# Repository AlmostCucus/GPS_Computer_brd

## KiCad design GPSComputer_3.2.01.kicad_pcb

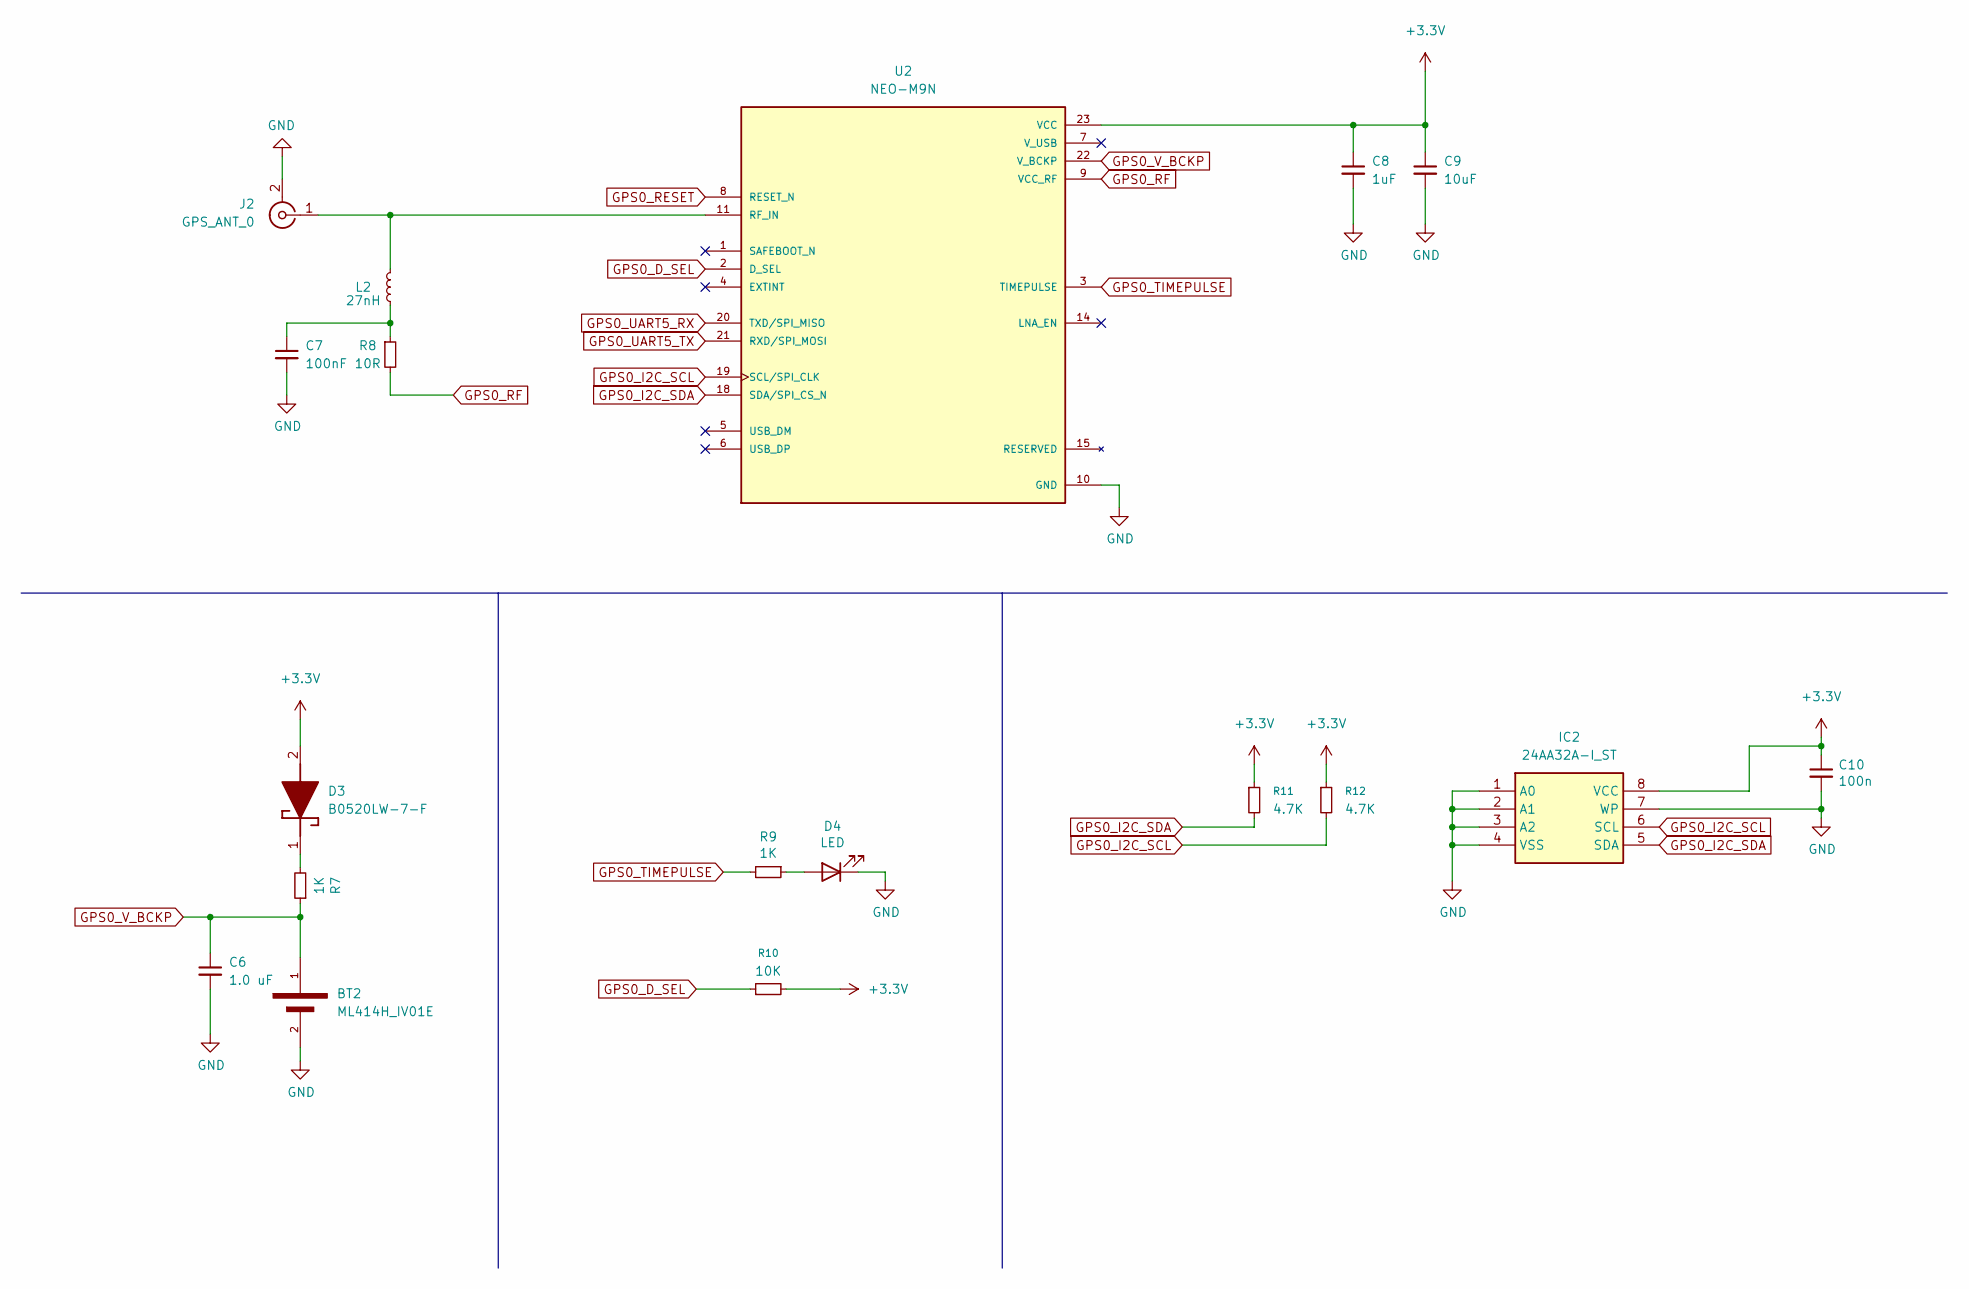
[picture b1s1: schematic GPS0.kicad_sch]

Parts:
BT2: ML414H_IV01E; SEIKO_ML414H_IV01E
C6: 1.0 uF; C_0805_2012Metric
C7: 100nF; C_0402_1005Metric
C8: 1uF; C_1210_3225Metric
C9: 10uF; C_1210_3225Metric
C10: 100n; C_0402_1005Metric
D3: B0520LW-7-F; SOD3716X145N; Manufacturer_Part_Number B0520LW-7-F; Mouser Part Number 621-B0520LW-F
D4: LED; LED_0805_2012Metric_Pad1.15x1.40mm_HandSolder
IC2: 24AA32A-I_ST; SOP65P640X120-8N; Manufacturer_Part_Number 24AA32A-I/ST; Mouser Part Number 579-24AA32A-I/ST
J2: GPS_ANT_0; SMA_Samtec_SMA-J-P-H-ST-EM1_EdgeMount
L2: 27nH; L_0402_1005Metric
R7, R9: 1K; R_0805_2012Metric
R8: 10R; R_0402_1005Metric
R10: 10K; R_0402_1005Metric
R11, R12: 4.7K; R_0402_1005Metric
U2: NEO-M9N; XCVR_NEO-M9N; PARTREV R05

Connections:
+3.3V: C8.1, C9.1, C10.1, D3.2 (A), IC2.8 (VCC), R10.2, R11.1, R12.1, U2.23 (VCC); also elsewhere on the board
GND: BT2.2, C6.2, C7.2, C8.2, C9.2, C10.2, D4.1 (K), IC2.1 (A0), IC2.2 (A1), IC2.3 (A2), IC2.4 (VSS), IC2.7 (WP), J2.2 (Ext), U2.10 (GND), U2.12 (GND), U2.13 (GND), U2.24 (GND); also elsewhere on the board
GPS0_D_SEL: R10.1, U2.2 (D_SEL)
GPS0_I2C_SCL: IC2.6 (SCL), R12.2, U2.19 (SCL/SPI_CLK)
GPS0_I2C_SDA: IC2.5 (SDA), R11.2, U2.18 (SDA/SPI_CS_N)
GPS0_RESET: U2.8 (RESET_N); also elsewhere on the board
GPS0_RF: R8.2, U2.9 (VCC_RF)
GPS0_TIMEPULSE: R9.2, U2.3 (TIMEPULSE)
GPS0_UART5_RX: U2.20 (TXD/SPI_MISO); also elsewhere on the board
GPS0_UART5_TX: U2.21 (RXD/SPI_MOSI); also elsewhere on the board
GPS0_V_BCKP: BT2.1, C6.1, R7.1, U2.22 (V_BCKP)
unnamed: C7.1, L2.1, R8.1
unnamed: D3.1 (K), R7.2
unnamed: D4.2 (A), R9.1
unnamed: J2.1 (In), L2.2, U2.11 (RF_IN)

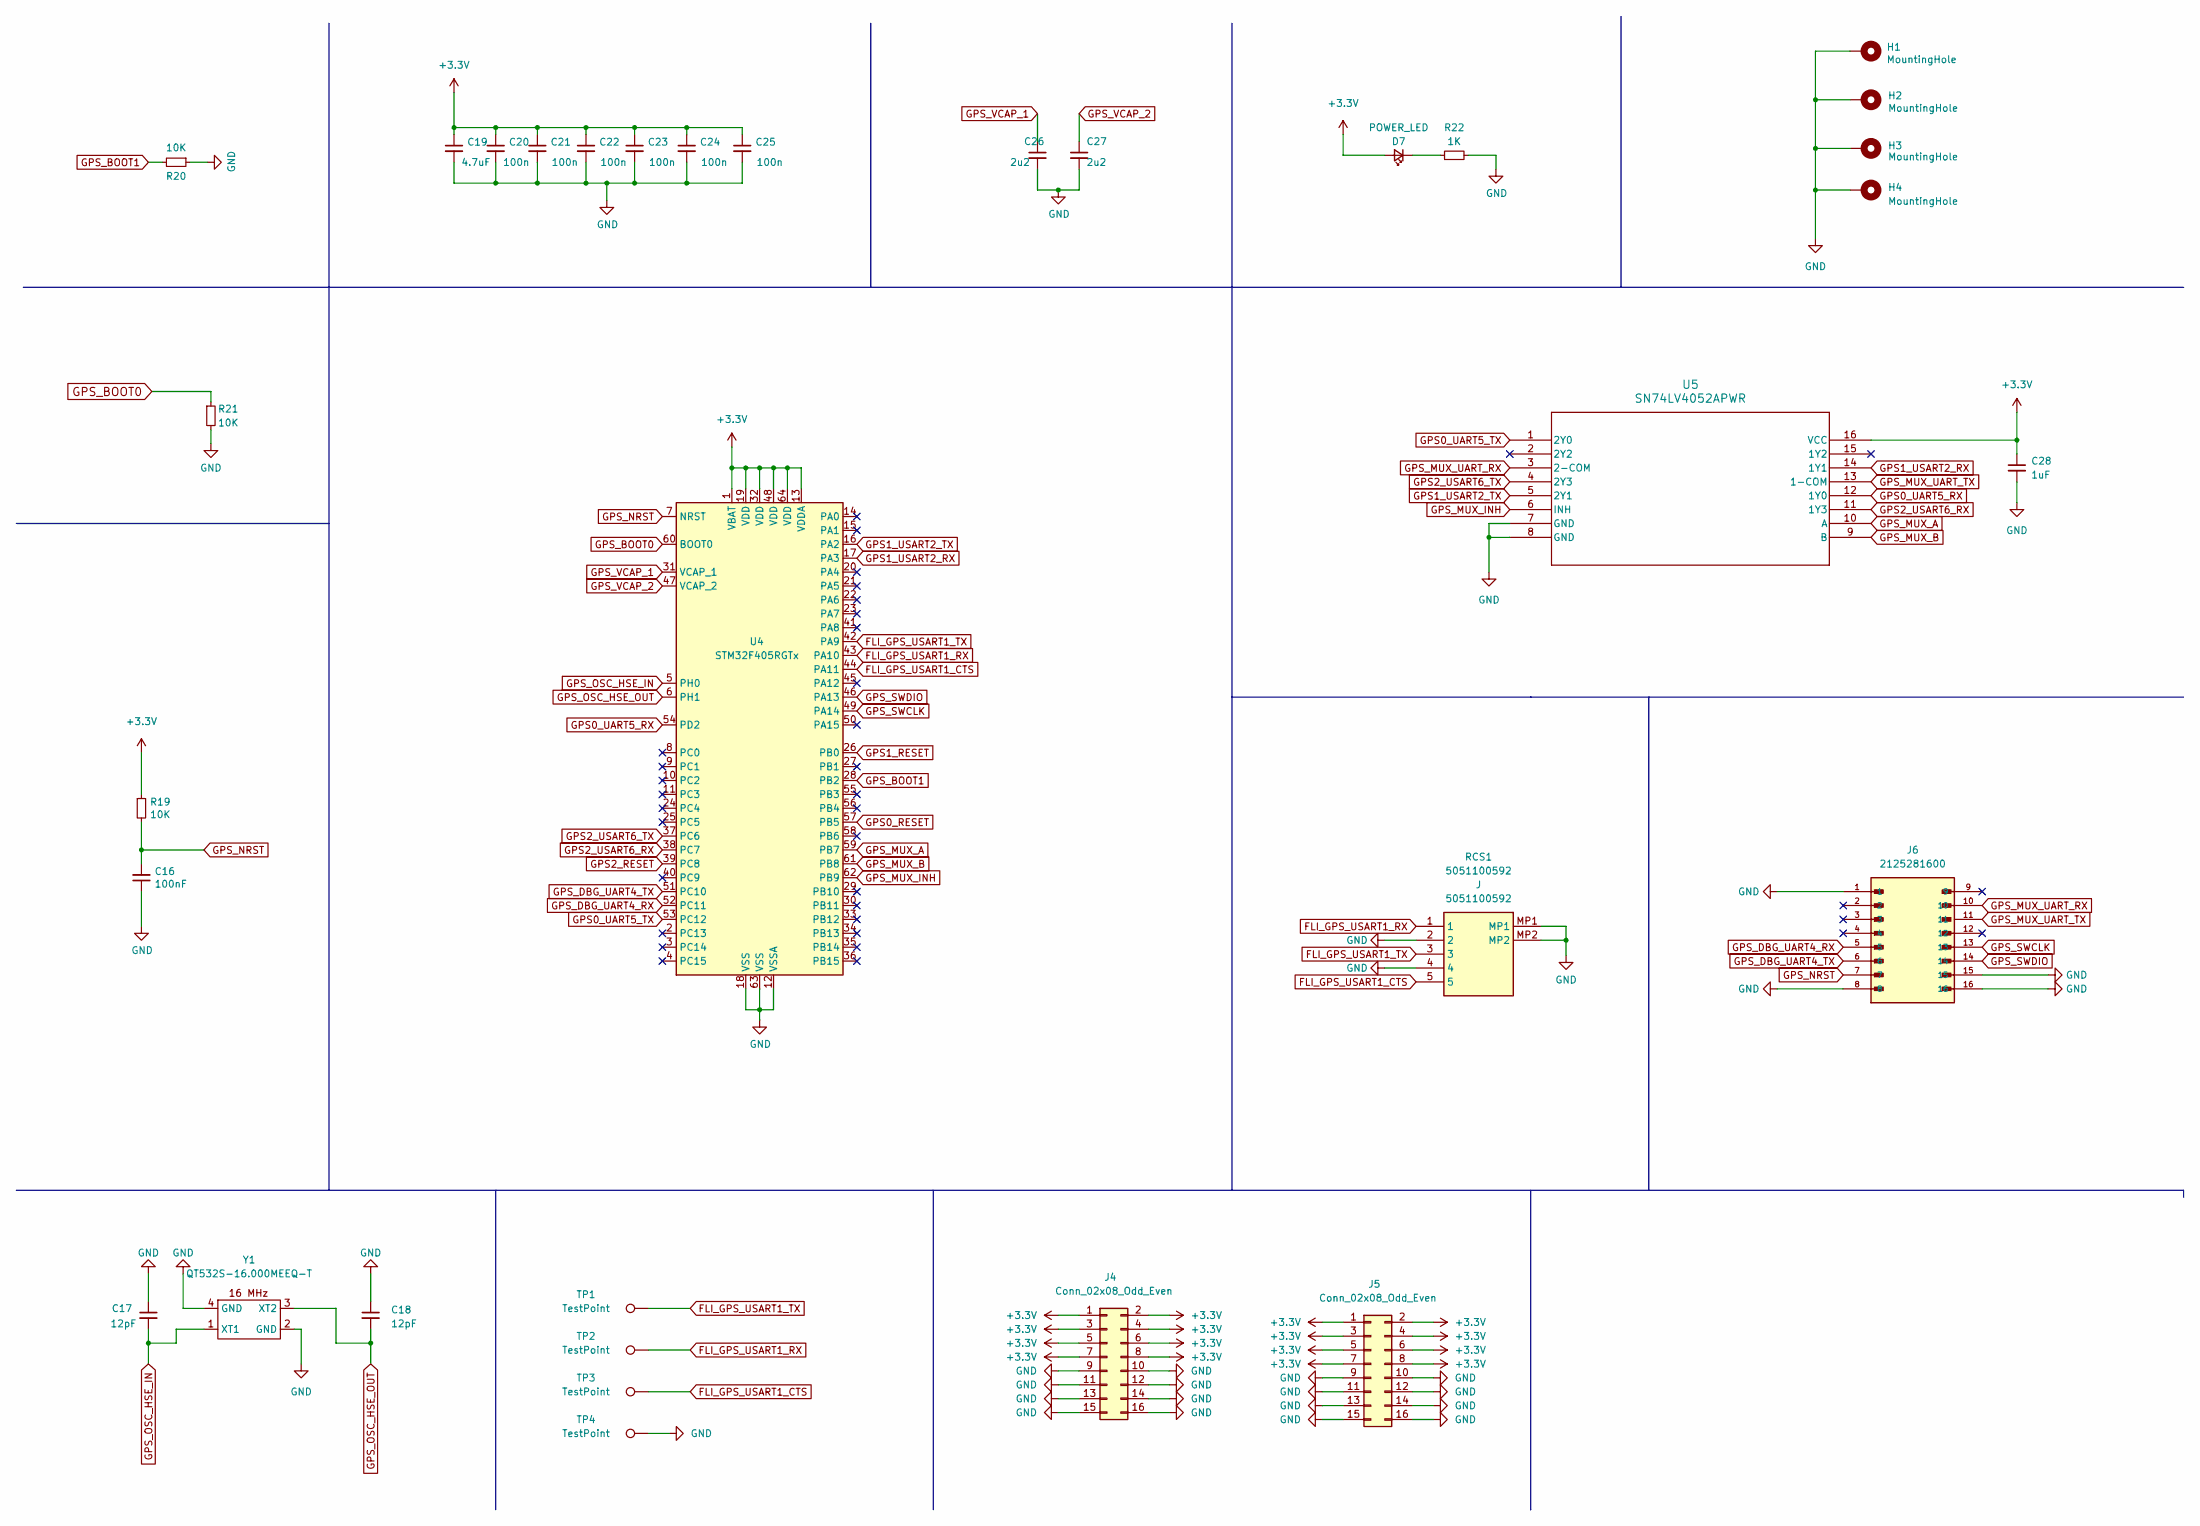
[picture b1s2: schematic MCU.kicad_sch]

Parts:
C16: 100nF; C_0402_1005Metric
C17, C18: 12pF; C_0402_1005Metric
C19: 4.7uF; C_0402_1005Metric
C20, C21, C22, C23, C24, C25: 100n; C_0402_1005Metric
C26, C27: 2u2; C_0603_1608Metric
C28: 1uF; C_0402_1005Metric
D7: POWER_LED; LED_0603_1608Metric
H1, H2, H3, H4: MountingHole; MountingHole_3.2mm_M3_Pad_Via
J4: Conn_02x08_Odd_Even; PinHeader_2x08_P2.54mm_Vertical_SMD
J5: Conn_02x08_Odd_Even; PinSocket_2x08_P2.54mm_Vertical_SMD
J6: 2125281600; MOLEX_2125281600; PARTREV A3
R19, R20, R21: 10K; R_0402_1005Metric
R22: 1K; R_0402_1005Metric
RCS1: 5051100592; Manufacturer_Part_Number 5051100592; Mouser Part Number N/A
TP1, TP2, TP3, TP4: TestPoint; TestPoint_Pad_D1.0mm
U4: STM32F405RGTx; LQFP-64_10x10mm_P0.5mm
U5: SN74LV4052APWR; PW16
Y1: QT532S-16.000MEEQ-T

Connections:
+3.3V: C19.1, C20.1, C21.1, C22.1, C23.1, C24.1, C25.1, C28.1, D7.2 (A), J4.1, J4.2, J4.3, J4.4, J4.5, J4.6, J4.7, J4.8, J5.1, J5.2, J5.3, J5.4, J5.5, J5.6, J5.7, J5.8, R19.1, U4.1 (VBAT), U4.13 (VDDA), U4.19 (VDD), U4.32 (VDD), U4.48 (VDD), U4.64 (VDD), U5.16 (VCC); also elsewhere on the board
FLI_GPS_USART1_CTS: RCS1.5, TP3.1 (1_1), U4.44 (PA11)
FLI_GPS_USART1_RX: RCS1.1, TP2.1 (1_1), U4.43 (PA10)
FLI_GPS_USART1_TX: RCS1.3, TP1.1 (1_1), U4.42 (PA9)
GND: C16.1, C17.1, C18.1, C19.2, C20.2, C21.2, C22.2, C23.2, C24.2, C25.2, C26.2, C27.2, C28.2, H1.1 (1_1), H2.1 (1_1), H3.1 (1_1), H4.1 (1_1), J4.9, J4.10, J4.11, J4.12, J4.13, J4.14, J4.15, J4.16, J5.9, J5.10, J5.11, J5.12, J5.13, J5.14, J5.15, J5.16, J6.1, J6.8, J6.15, J6.16, R20.1, R21.2, R22.2, RCS1.2, RCS1.4, RCS1.MP1, RCS1.MP2, TP4.1 (1_1), U4.12 (VSSA), U4.18 (VSS), U4.63 (VSS), U5.7 (GND), U5.8 (GND), Y1.2 (GND), Y1.4 (GND); also elsewhere on the board
GPS0_RESET: U4.57 (PB5); also elsewhere on the board
GPS0_UART5_RX: U4.54 (PD2), U5.12 (1Y0); also elsewhere on the board
GPS0_UART5_TX: U4.53 (PC12), U5.1 (2Y0); also elsewhere on the board
GPS1_RESET: U4.26 (PB0); also elsewhere on the board
GPS1_USART2_RX: U4.17 (PA3), U5.14 (1Y1); also elsewhere on the board
GPS1_USART2_TX: U4.16 (PA2), U5.5 (2Y1); also elsewhere on the board
GPS2_RESET: U4.39 (PC8); also elsewhere on the board
GPS2_USART6_RX: U4.38 (PC7), U5.11 (1Y3); also elsewhere on the board
GPS2_USART6_TX: U4.37 (PC6), U5.4 (2Y3); also elsewhere on the board
GPS_BOOT0: R21.1, U4.60 (BOOT0)
GPS_BOOT1: R20.2, U4.28 (PB2)
GPS_DBG_UART4_RX: J6.5, U4.52 (PC11)
GPS_DBG_UART4_TX: J6.6, U4.51 (PC10)
GPS_MUX_A: U4.59 (PB7), U5.10 (A)
GPS_MUX_B: U4.61 (PB8), U5.9 (B)
GPS_MUX_INH: U4.62 (PB9), U5.6 (INH)
GPS_MUX_UART_RX: J6.10, U5.3 (2-COM)
GPS_MUX_UART_TX: J6.11, U5.13 (1-COM)
GPS_NRST: C16.2, J6.7, R19.2, U4.7 (NRST)
GPS_OSC_HSE_IN: C17.2, U4.5 (PH0), Y1.1 (XT1)
GPS_OSC_HSE_OUT: C18.2, U4.6 (PH1), Y1.3 (XT2)
GPS_SWCLK: J6.13, U4.49 (PA14)
GPS_SWDIO: J6.14, U4.46 (PA13)
GPS_VCAP_1: C26.1, U4.31 (VCAP_1)
GPS_VCAP_2: C27.1, U4.47 (VCAP_2)
unnamed: D7.1 (K), R22.1

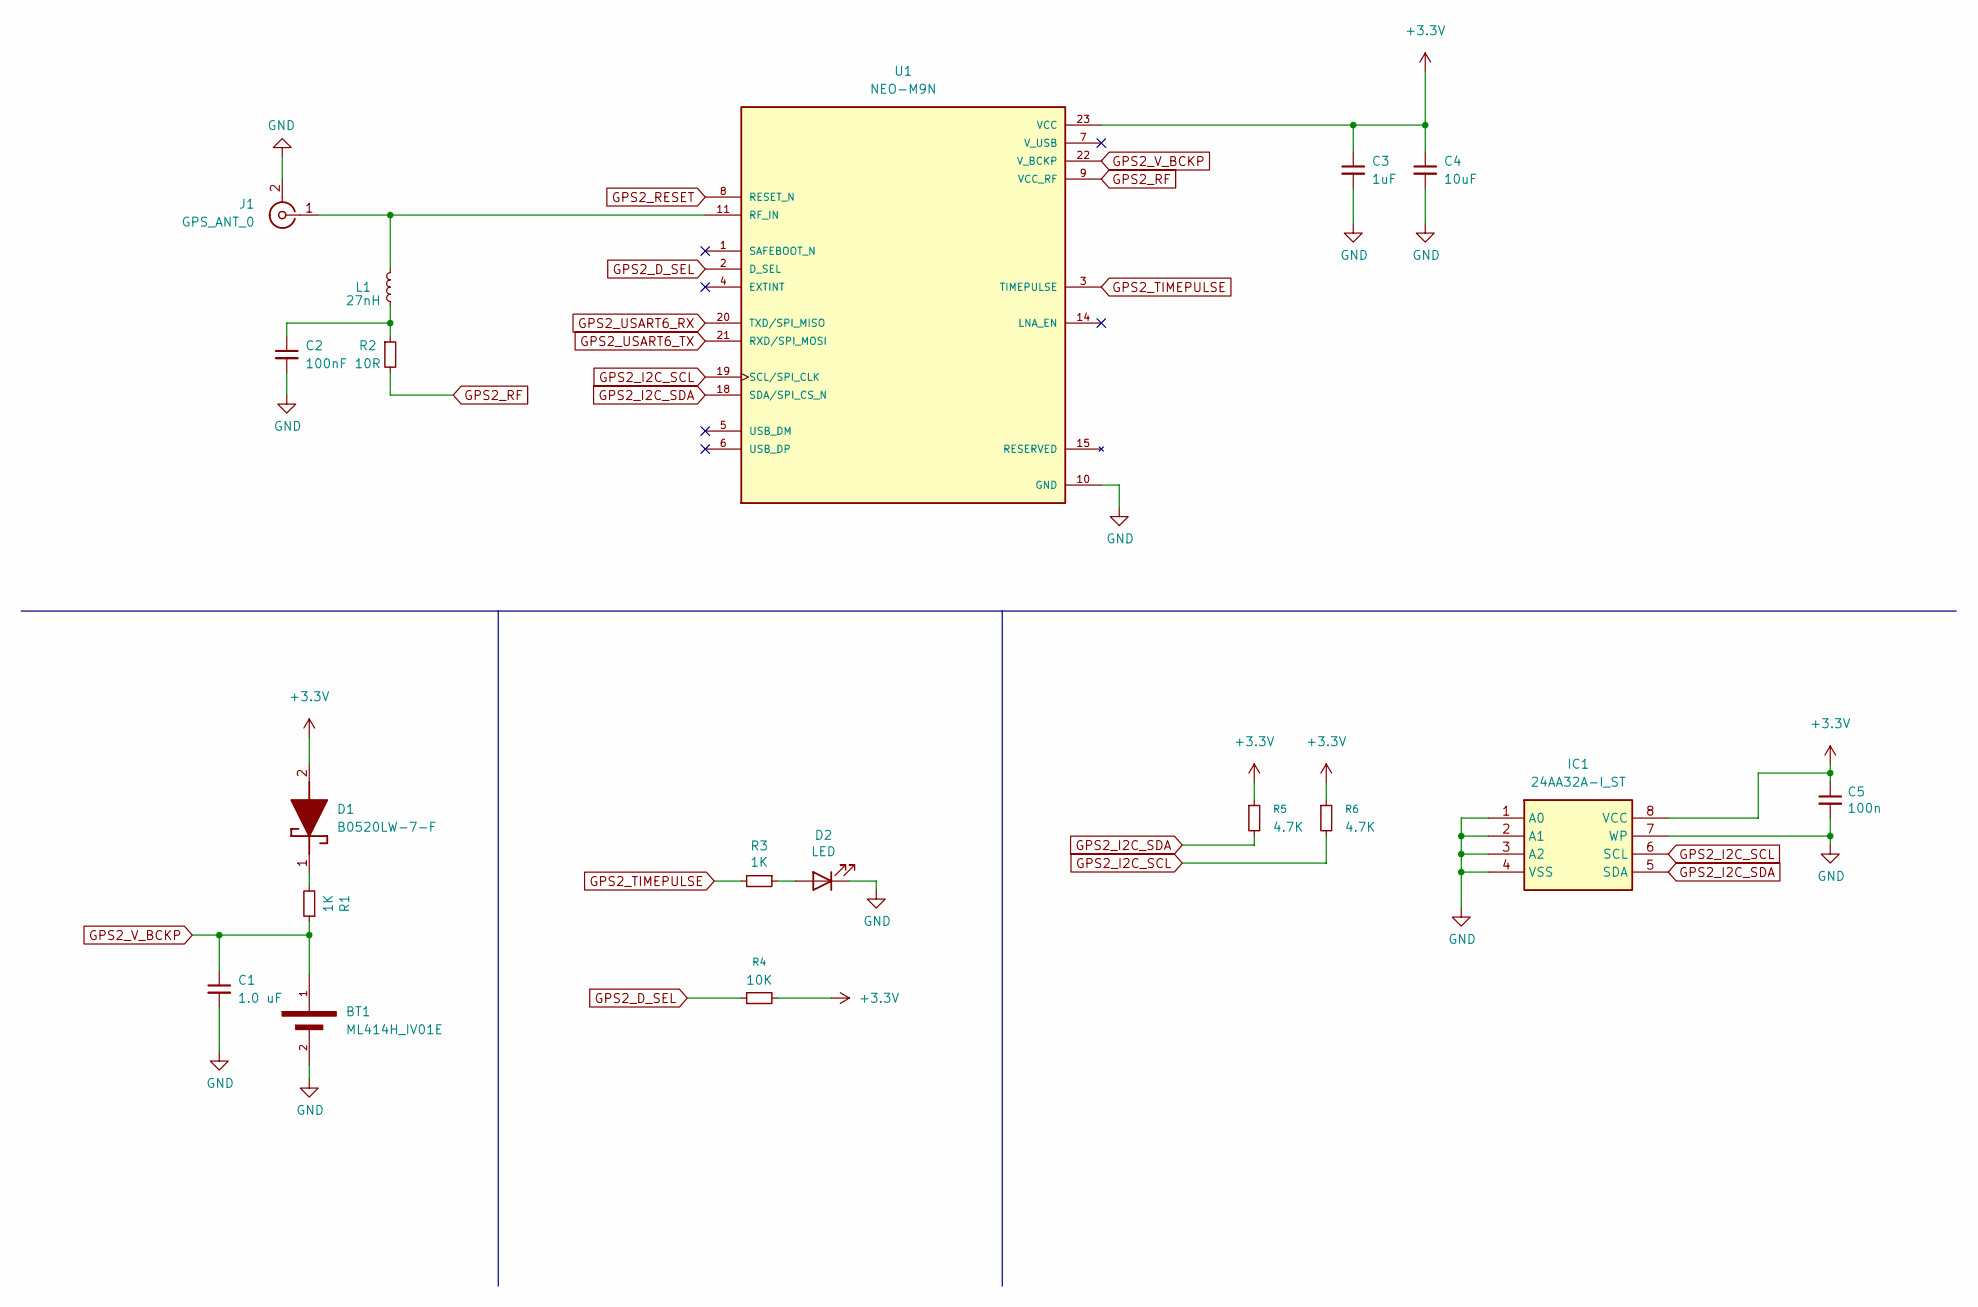
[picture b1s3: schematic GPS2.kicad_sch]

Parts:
BT1: ML414H_IV01E; SEIKO_ML414H_IV01E
C1: 1.0 uF; C_0805_2012Metric
C2: 100nF; C_0402_1005Metric
C3: 1uF; C_1210_3225Metric
C4: 10uF; C_1210_3225Metric
C5: 100n; C_0402_1005Metric
D1: B0520LW-7-F; SOD3716X145N; Manufacturer_Part_Number B0520LW-7-F; Mouser Part Number 621-B0520LW-F
D2: LED; LED_0805_2012Metric_Pad1.15x1.40mm_HandSolder
IC1: 24AA32A-I_ST; SOP65P640X120-8N; Manufacturer_Part_Number 24AA32A-I/ST; Mouser Part Number 579-24AA32A-I/ST
J1: GPS_ANT_0; SMA_Samtec_SMA-J-P-H-ST-EM1_EdgeMount
L1: 27nH; L_0402_1005Metric
R1, R3: 1K; R_0805_2012Metric
R2: 10R; R_0402_1005Metric
R4: 10K; R_0402_1005Metric
R5, R6: 4.7K; R_0402_1005Metric
U1: NEO-M9N; XCVR_NEO-M9N; PARTREV R05

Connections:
+3.3V: C3.1, C4.1, C5.1, D1.2 (A), IC1.8 (VCC), R4.2, R5.1, R6.1, U1.23 (VCC); also elsewhere on the board
GND: BT1.2, C1.2, C2.2, C3.2, C4.2, C5.2, D2.1 (K), IC1.1 (A0), IC1.2 (A1), IC1.3 (A2), IC1.4 (VSS), IC1.7 (WP), J1.2 (Ext), U1.10 (GND), U1.12 (GND), U1.13 (GND), U1.24 (GND); also elsewhere on the board
GPS2_D_SEL: R4.1, U1.2 (D_SEL)
GPS2_I2C_SCL: IC1.6 (SCL), R6.2, U1.19 (SCL/SPI_CLK)
GPS2_I2C_SDA: IC1.5 (SDA), R5.2, U1.18 (SDA/SPI_CS_N)
GPS2_RESET: U1.8 (RESET_N); also elsewhere on the board
GPS2_RF: R2.2, U1.9 (VCC_RF)
GPS2_TIMEPULSE: R3.2, U1.3 (TIMEPULSE)
GPS2_USART6_RX: U1.20 (TXD/SPI_MISO); also elsewhere on the board
GPS2_USART6_TX: U1.21 (RXD/SPI_MOSI); also elsewhere on the board
GPS2_V_BCKP: BT1.1, C1.1, R1.1, U1.22 (V_BCKP)
unnamed: C2.1, L1.1, R2.1
unnamed: D1.1 (K), R1.2
unnamed: D2.2 (A), R3.1
unnamed: J1.1 (In), L1.2, U1.11 (RF_IN)

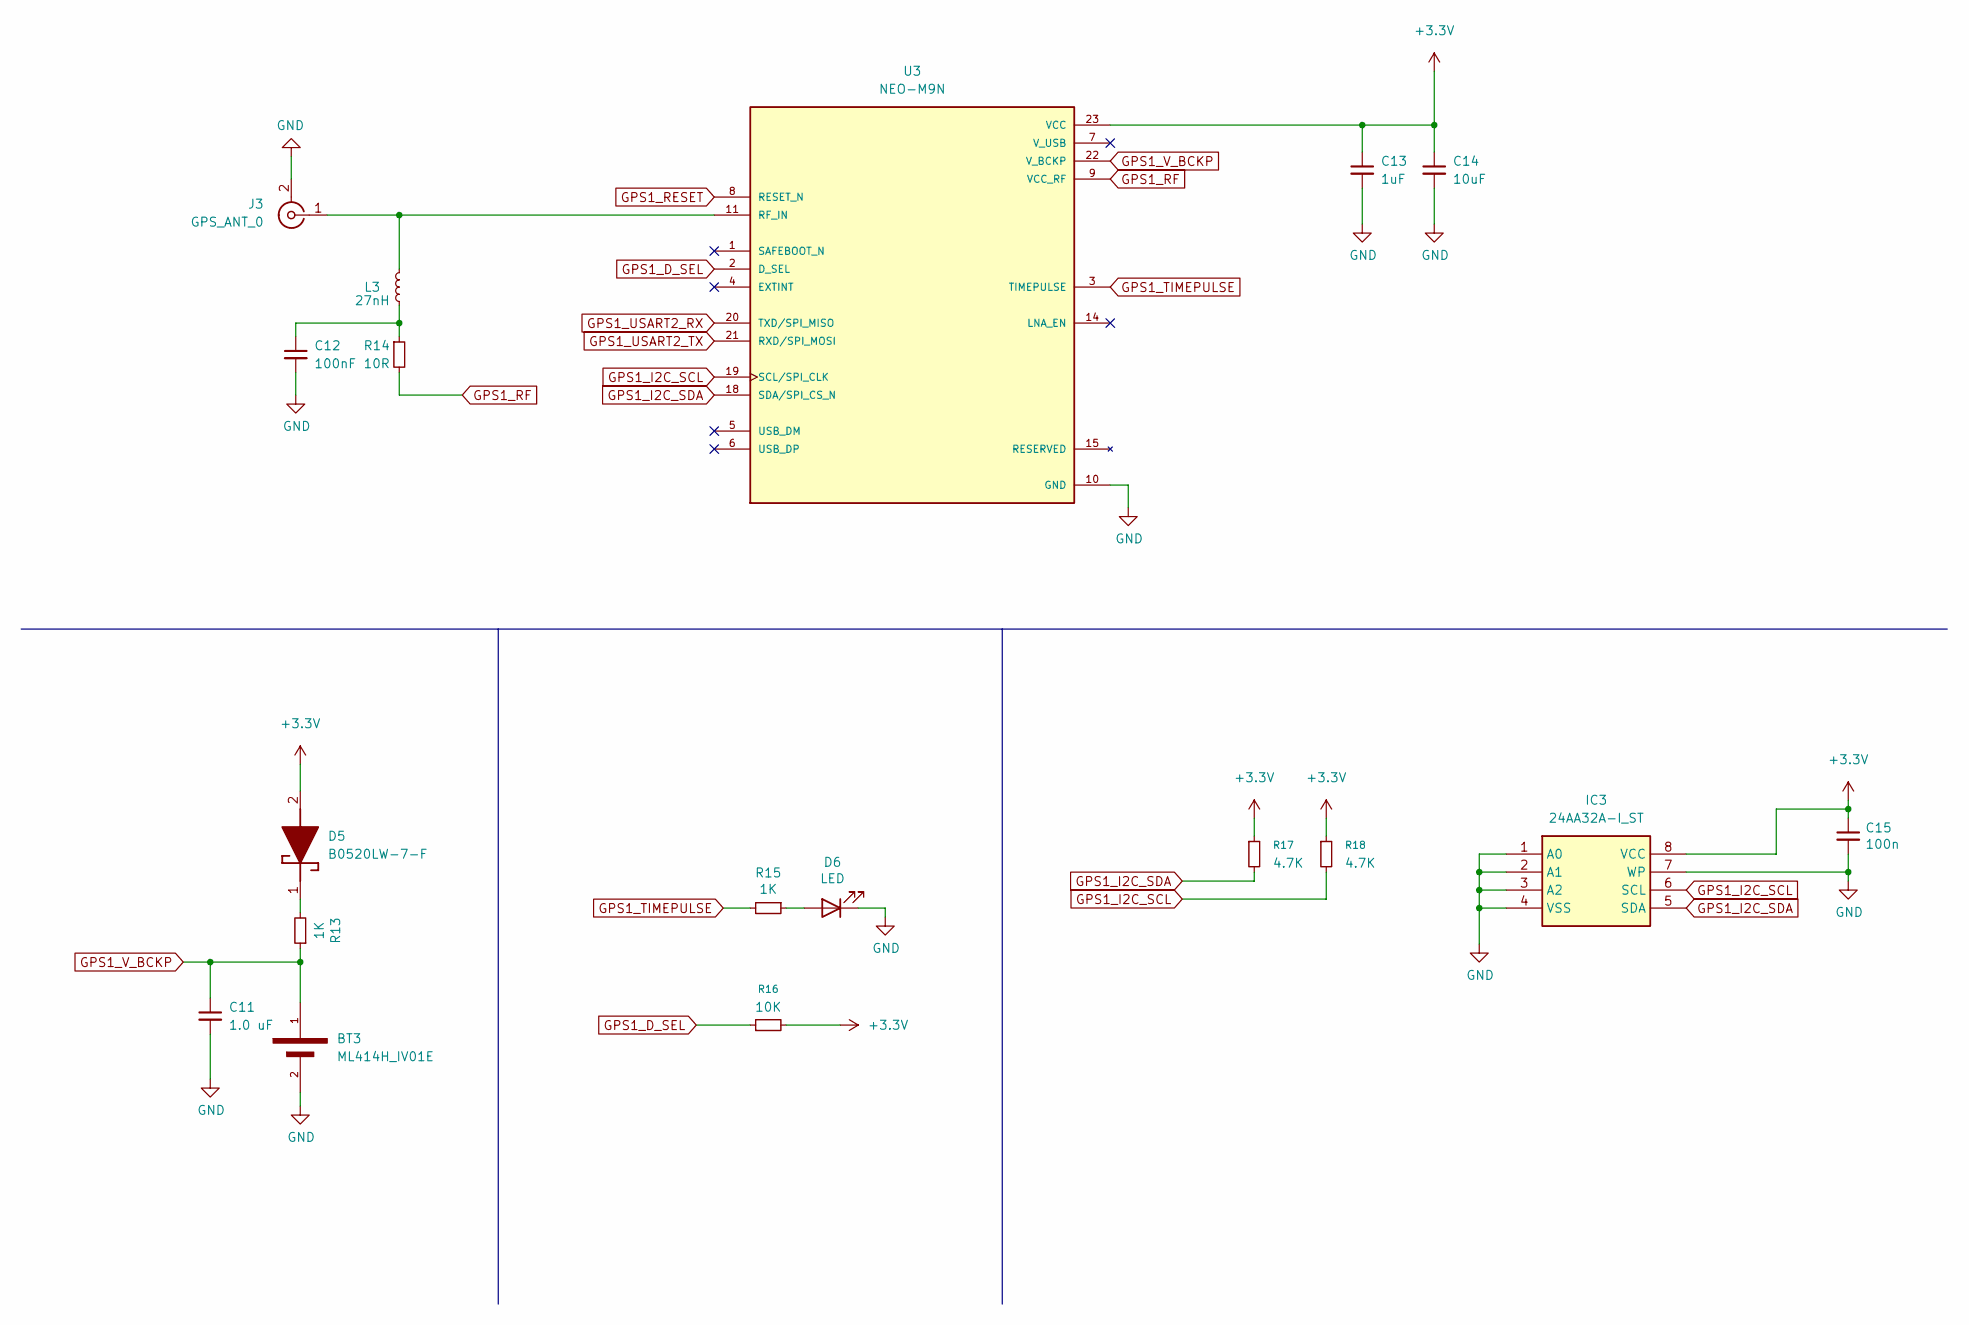
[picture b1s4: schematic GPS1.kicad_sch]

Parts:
BT3: ML414H_IV01E; SEIKO_ML414H_IV01E
C11: 1.0 uF; C_0805_2012Metric
C12: 100nF; C_0402_1005Metric
C13: 1uF; C_1210_3225Metric
C14: 10uF; C_1210_3225Metric
C15: 100n; C_0402_1005Metric
D5: B0520LW-7-F; SOD3716X145N; Manufacturer_Part_Number B0520LW-7-F; Mouser Part Number 621-B0520LW-F
D6: LED; LED_0805_2012Metric_Pad1.15x1.40mm_HandSolder
IC3: 24AA32A-I_ST; SOP65P640X120-8N; Manufacturer_Part_Number 24AA32A-I/ST; Mouser Part Number 579-24AA32A-I/ST
J3: GPS_ANT_0; SMA_Samtec_SMA-J-P-H-ST-EM1_EdgeMount
L3: 27nH; L_0402_1005Metric
R13, R15: 1K; R_0805_2012Metric
R14: 10R; R_0402_1005Metric
R16: 10K; R_0402_1005Metric
R17, R18: 4.7K; R_0402_1005Metric
U3: NEO-M9N; XCVR_NEO-M9N; PARTREV R05

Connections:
+3.3V: C13.1, C14.1, C15.1, D5.2 (A), IC3.8 (VCC), R16.2, R17.1, R18.1, U3.23 (VCC); also elsewhere on the board
GND: BT3.2, C11.2, C12.2, C13.2, C14.2, C15.2, D6.1 (K), IC3.1 (A0), IC3.2 (A1), IC3.3 (A2), IC3.4 (VSS), IC3.7 (WP), J3.2 (Ext), U3.10 (GND), U3.12 (GND), U3.13 (GND), U3.24 (GND); also elsewhere on the board
GPS1_D_SEL: R16.1, U3.2 (D_SEL)
GPS1_I2C_SCL: IC3.6 (SCL), R18.2, U3.19 (SCL/SPI_CLK)
GPS1_I2C_SDA: IC3.5 (SDA), R17.2, U3.18 (SDA/SPI_CS_N)
GPS1_RESET: U3.8 (RESET_N); also elsewhere on the board
GPS1_RF: R14.2, U3.9 (VCC_RF)
GPS1_TIMEPULSE: R15.2, U3.3 (TIMEPULSE)
GPS1_USART2_RX: U3.20 (TXD/SPI_MISO); also elsewhere on the board
GPS1_USART2_TX: U3.21 (RXD/SPI_MOSI); also elsewhere on the board
GPS1_V_BCKP: BT3.1, C11.1, R13.1, U3.22 (V_BCKP)
unnamed: C12.1, L3.1, R14.1
unnamed: D5.1 (K), R13.2
unnamed: D6.2 (A), R15.1
unnamed: J3.1 (In), L3.2, U3.11 (RF_IN)

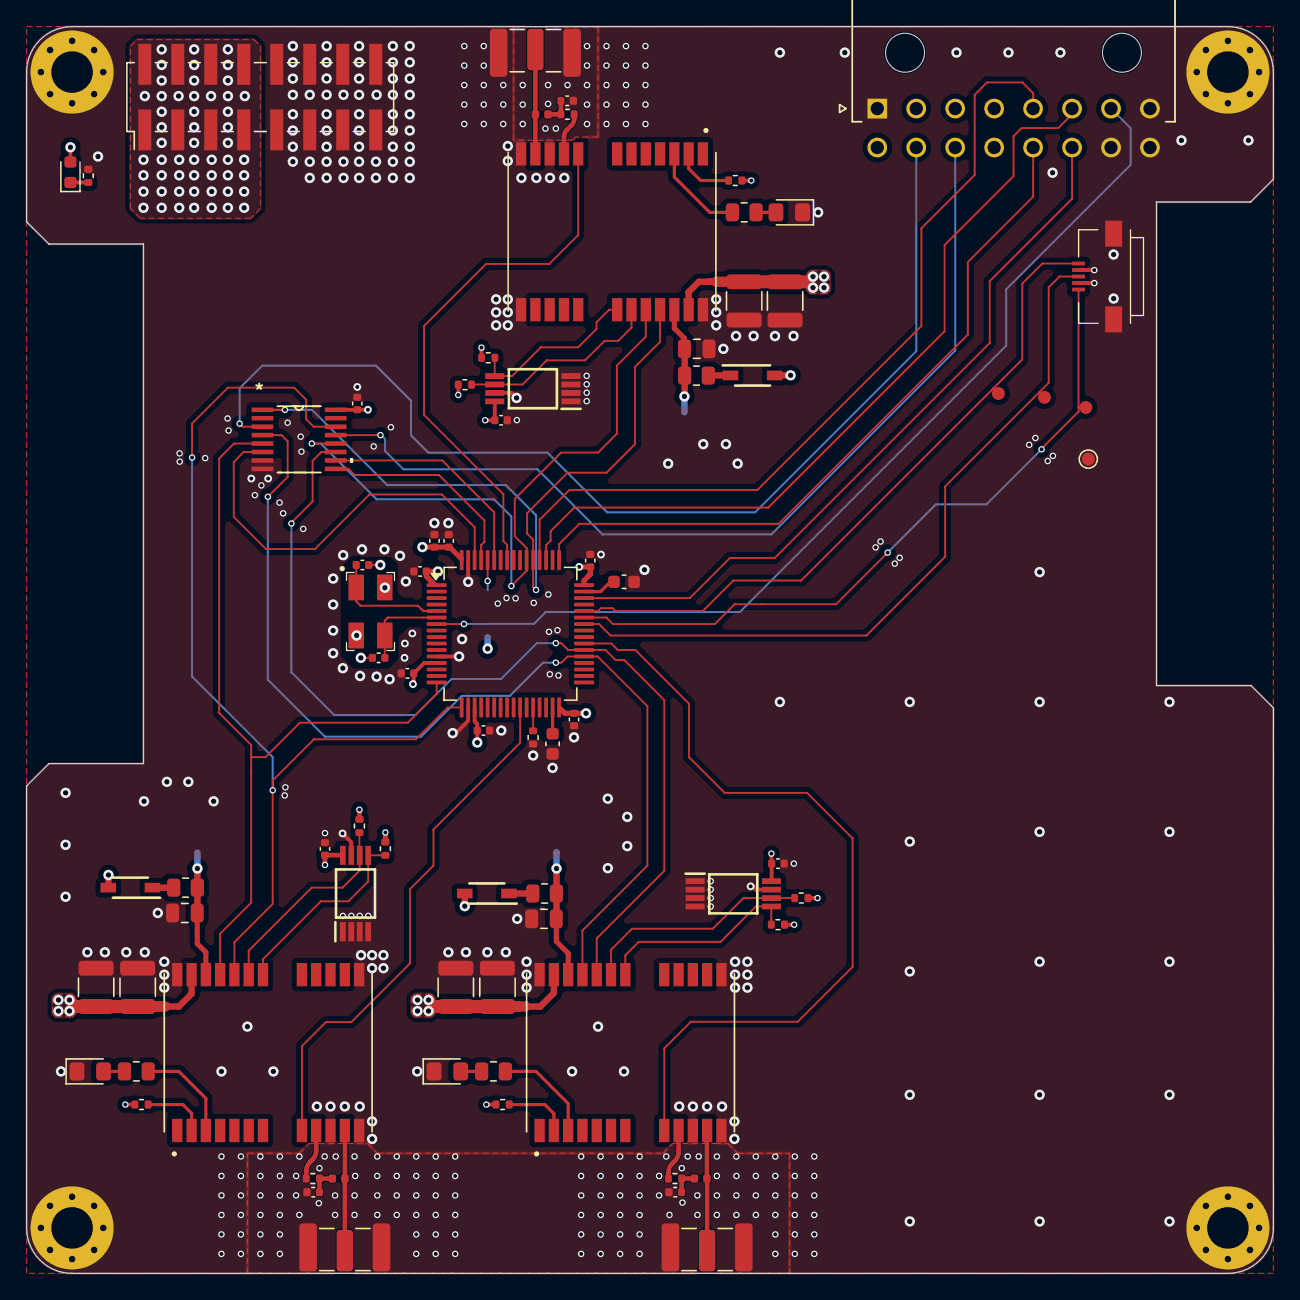
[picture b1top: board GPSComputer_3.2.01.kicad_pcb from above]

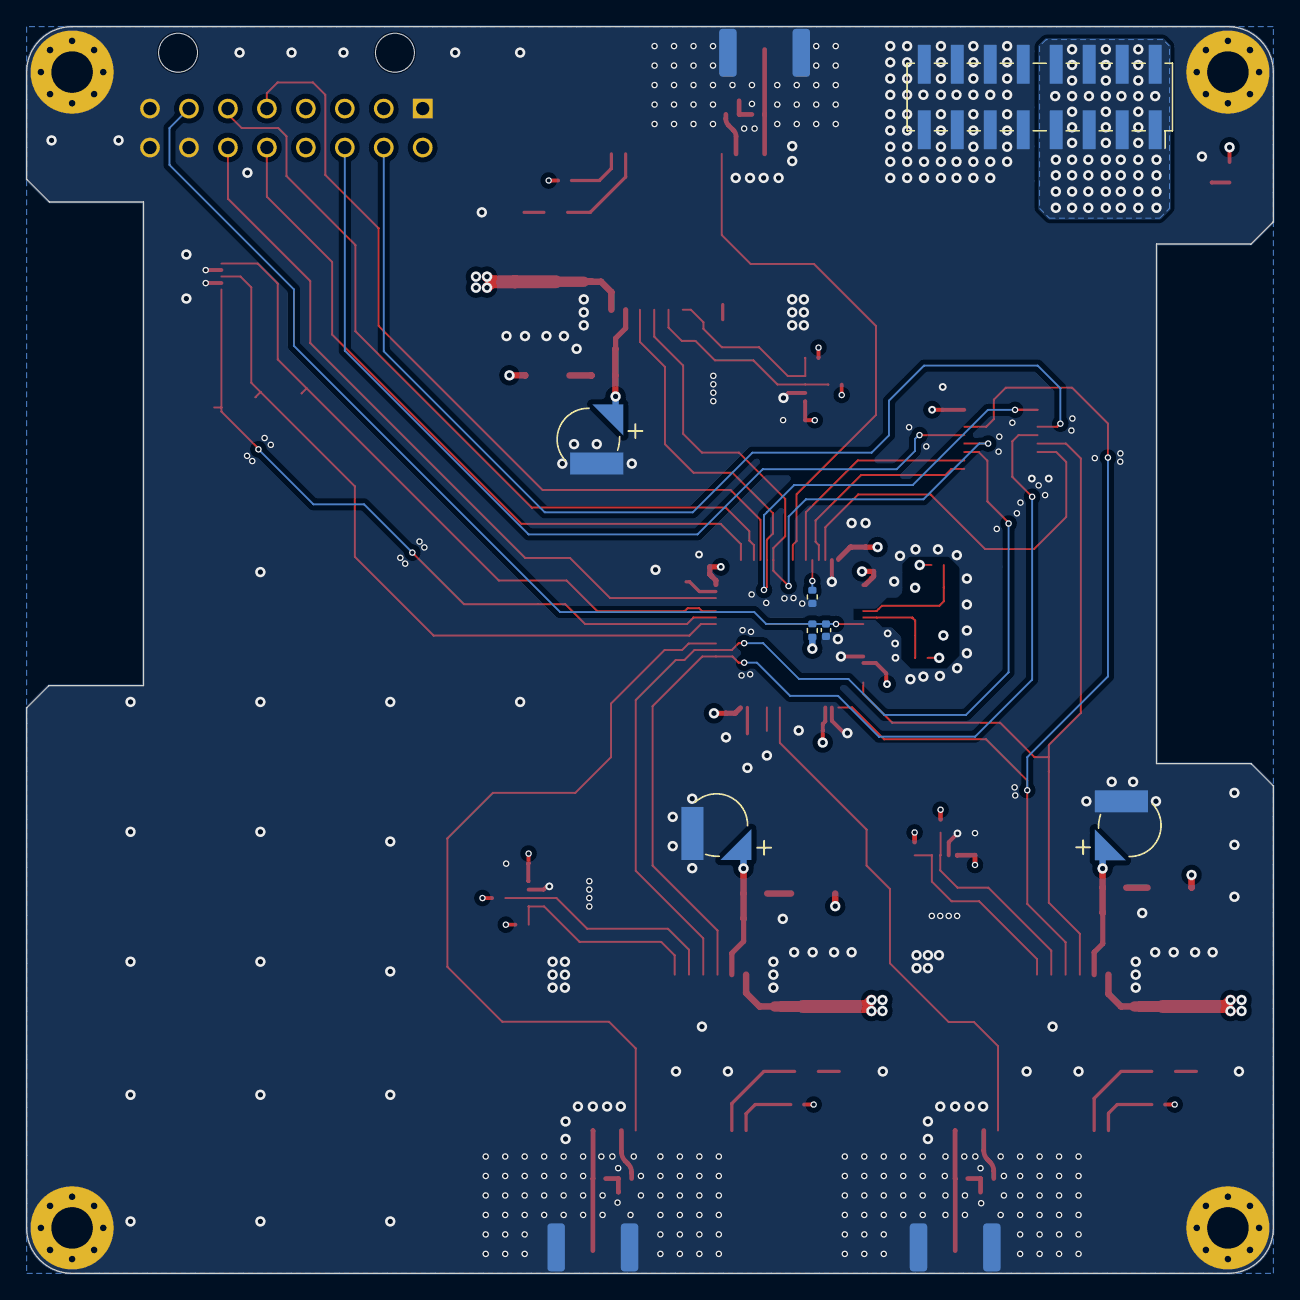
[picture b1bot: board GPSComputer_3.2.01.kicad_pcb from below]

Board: 4 copper layers, 96.0 x 96.0 mm, 87 parts (7 on the bottom side), 61 nets.

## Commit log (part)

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2025-06-18 MAX-M10S-00B
2025-06-18 Adding M10
2025-06-19 Finished M10
2025-06-19 Adding RF
2025-06-20 Corrected battery position
2026-03-03 Last commit
2026-03-08 Second commit
2026-04-12 Correcet MUX pins
